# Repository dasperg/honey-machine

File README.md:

# honey-machine

## Installation

## Components
- Board: DOIT ESP32 DEVKIT V1
- Coin acceptor
- Arduino 2 relay shield

## Usage

## Contributing

## License
[MIT](https://choosealicense.com/licenses/mit/)

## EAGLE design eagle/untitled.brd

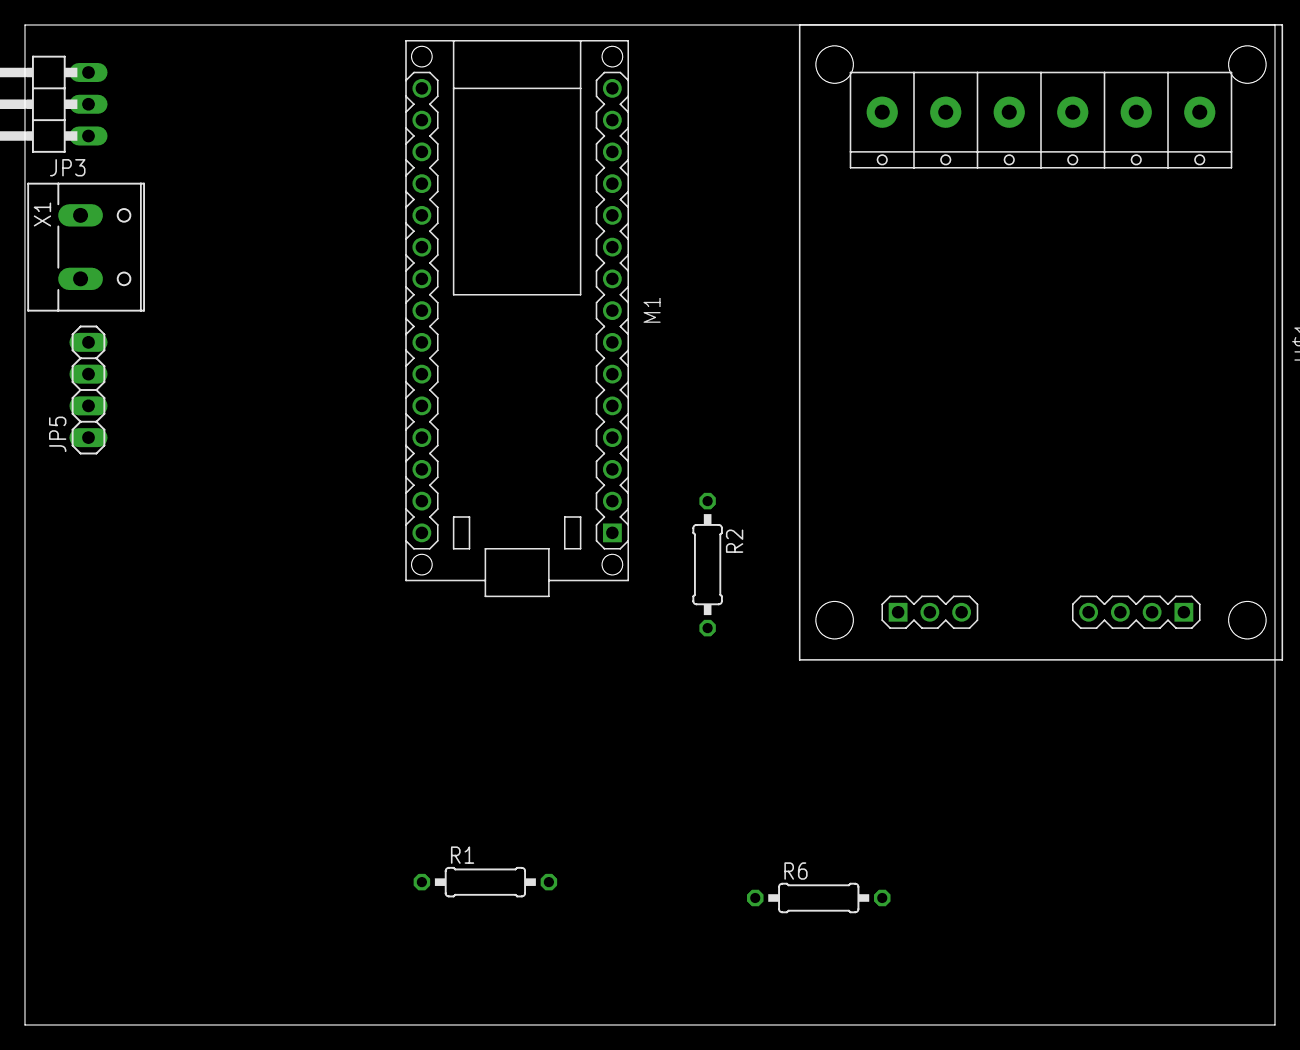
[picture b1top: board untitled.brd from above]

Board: 2 copper layers, 100.0 x 80.0 mm, 8 parts (0 on the bottom side), 7 nets, no tracks yet.

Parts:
JP3: CoinMachine; 1X03/90
JP5: Display; 1X04
M1: ARDUINO-NANO-3.0
R1, R2, R6: 10k; 0207/10
U$1: RELAY-2-SRD#RC
X1: W237-132

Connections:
GND: JP3.3, JP5.3, M1.J1.14, M1.J2.14, R1.1, U$1.J1.4, U$1.J2.3, U$1.P1.3, U$1.P1.6, X1.2
unnamed: JP3.2, M1.J2.7, R6.1
unnamed: M1.J1.2, R1.2, R2.1
unnamed: M1.J1.8, U$1.J1.2
unnamed: M1.J1.9, U$1.J1.3
unnamed: U$1.J2.1, U$1.J2.2
VCC: JP3.1, JP5.4, M1.J1.15, M1.J2.15, R2.2, R6.2, U$1.J1.1, U$1.P1.1, U$1.P1.4, X1.1

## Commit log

2020-07-15 Checkpoint
2020-08-10 arduino files & add eagle project
2020-08-11 Add README.md
2020-08-11 #Eagle - Change Arduino symbol
2020-08-12 Add "Components" paragraph to README.md
2020-08-15 Add readVoltage & rearange code
2020-08-15 Move config.h into arduino folder

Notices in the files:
parts and their libraries:
diy-modules: Released under the Creative Commons Attribution 4.0 International License: http://creativecommons.org/licenses/by/4.0
